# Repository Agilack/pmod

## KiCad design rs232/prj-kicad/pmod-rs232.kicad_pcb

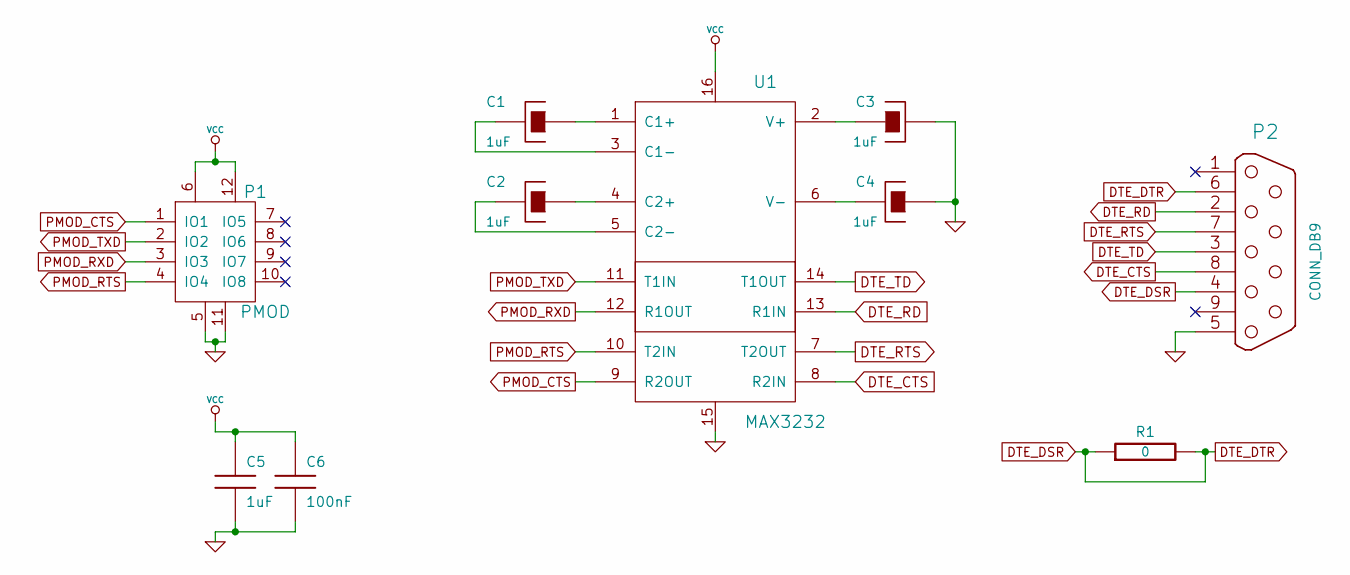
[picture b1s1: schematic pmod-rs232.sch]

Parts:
C1, C2, C3, C4, C5: 1uF; SMD0603
C6: 100nF; SMD0603
P1: PMOD; CONN_PMOD-Male
P2: CONN_DB9; CONN_SUBD-1634218
R1: 0; SMD0603
U1: MAX3232; TSSOP16

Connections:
DTE_CTS: P2.8, U1.8 (R2IN)
DTE_DSR: P2.4, P2.6, R1.1, R1.2
DTE_RD: P2.2, U1.13 (R1IN)
DTE_RTS: P2.7, U1.7 (T2OUT)
DTE_TD: P2.3, U1.14 (T1OUT)
GND: C3.2, C4.1, C5.2, C6.2, P1.5, P1.11, P2.5, U1.15
unnamed: C1.1, U1.1 (C1+)
unnamed: C1.2, U1.3 (C1-)
unnamed: C2.1, U1.4 (C2+)
unnamed: C2.2, U1.5 (C2-)
unnamed: C3.1, U1.2 (V+)
unnamed: C4.2, U1.6 (V-)
PMOD_CTS: P1.1 (IO1), U1.9 (R2OUT)
PMOD_RTS: P1.4 (IO4), U1.10 (T2IN)
PMOD_RXD: P1.3 (IO3), U1.12 (R1OUT)
PMOD_TXD: P1.2 (IO2), U1.11 (T1IN)
VCC: C5.1, C6.1, P1.6, P1.12, U1.16

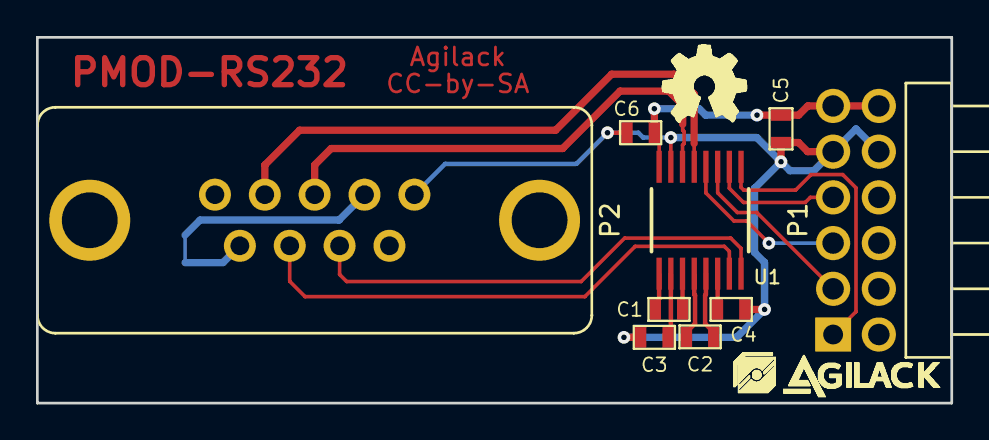
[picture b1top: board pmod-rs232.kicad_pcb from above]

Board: 2 copper layers, 50.8 x 20.3 mm, 12 parts (1 on the bottom side), 17 nets.

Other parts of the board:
agilack-11.5: 450px; agilack-11.5
ohw_logo: VAL**; ohw-logo

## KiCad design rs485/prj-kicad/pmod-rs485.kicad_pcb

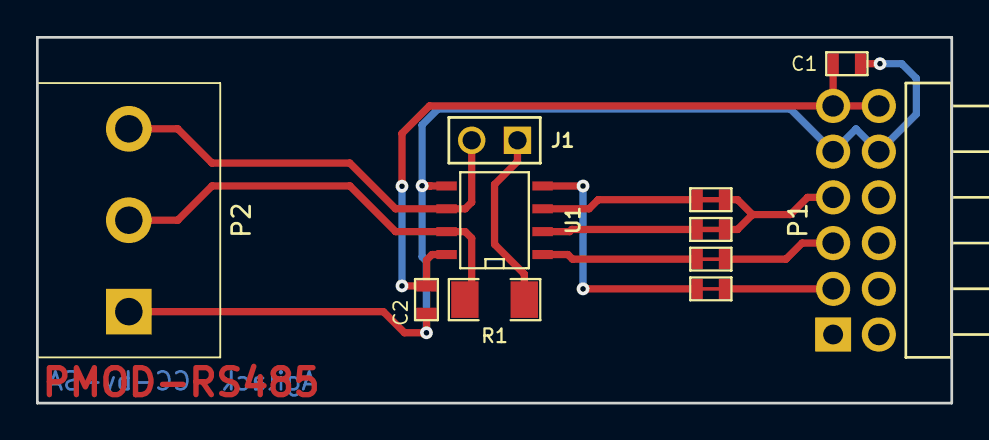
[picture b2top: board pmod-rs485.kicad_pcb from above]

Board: 2 copper layers, 50.8 x 20.3 mm, 11 parts (0 on the bottom side), 8 nets.

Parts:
C1, C2: 1uF; SMD0603
J1: JUMPER; CONN_2
P1: PMOD; CONN_PMOD-Male
P2: CONN_3; CONN_MC000035
R1: 120; SMD1206
R2, R3, R4, R5: 0; SMD0603
U1: SN65HVD72; SMD_SO8E

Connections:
+3.3V: C1.1, C2.1, P1.6, P1.12, U1.8
/RS485_A: J1.2, P2.3, U1.6
/RS485_B: P2.2, R1.1, U1.7
GND: C1.2, C2.2, P1.5, P1.11, P2.1, U1.5
unnamed: J1.1, R1.2
PMOD_CLK: P1.4, R4.1, R4.2, R5.1, R5.2, U1.2, U1.3
PMOD_RX: P1.3, R3.1, R3.2, U1.1
PMOD_TX: P1.2, R2.1, R2.2, U1.4

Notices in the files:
rs232/prj-kicad/pmod-rs232.kicad_pcb:
CC-by-SA
